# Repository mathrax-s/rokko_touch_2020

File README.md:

# rokko_touch_2020
EAGLE and KiCad files (PSoC4 flexible touch sensor)

</img>

</img>

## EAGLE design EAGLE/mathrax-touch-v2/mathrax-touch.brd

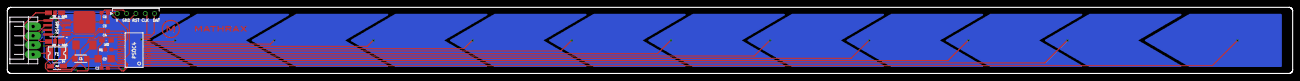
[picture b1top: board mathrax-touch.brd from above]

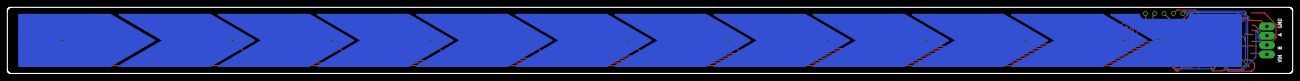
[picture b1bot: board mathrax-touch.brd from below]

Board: 2 copper layers, 350.0 x 18.0 mm, 31 parts (12 on the bottom side), 35 nets.

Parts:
C1: 0.33uF; 3216
C2, C5, C6: 0.1uF; 0603
C3: 22uF; 1210
C4: 2.2nF; 0603
F1: H1; RESETABLE-HUES
LED: LED; CHIPLED_0805
PSOC4: PSoC4; SSOP28
R1: 1k; 0603
RS485: RS485; SOIC127P600X175-8N
U$1: PINHEADER-5; PINHEADER-5L
U$2: TOUCH-PTN-3; TOUCH-PTN3
U$3, U$4, U$5, U$6, U$7, U$8, U$9, U$18, U$19, U$20: TOUCH-PTN-2; TOUCH-PTN2
U$11: EH4-UART
U$13: REGULATOR-TO252-3; BA33BC0FP
U$21: TOUCH-PTN-1; TOUCH-PTN1
U$22: DIODE-SS2040L
U$23, U$24: JUMPER
U$25: M-LOGO
U$27: MATHRAX-LOGO

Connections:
3.3V: C3.1, C5.1, C6.1, PSOC4.27, RS485.8, U$1.1, U$13.OUT
A: RS485.6, U$11.2, U$24.3
B: RS485.7, U$11.3, U$23.3
CLK: PSOC4.14, U$1.4
DAT: PSOC4.13, U$1.5
GND: C1.P$2, C2.2, C3.2, C4.2, C5.2, C6.2, LED.C, PSOC4.28, RS485.5, U$1.2, U$11.1, U$13.GND
LED: PSOC4.21, R1.1
unnamed: F1.1, U$22.P$1
unnamed: U$25.P$1, U$25.P$2
unnamed: U$27.1, U$27.2
unnamed: U$27.3, U$27.4
unnamed: U$27.5, U$27.6
unnamed: LED.A, R1.2
unnamed: C4.1, PSOC4.17
unnamed: C2.1, PSOC4.26
unnamed: C1.P$1, U$13.VIN, U$22.P$2
RS485-CE: PSOC4.18, RS485.2, RS485.3
RST: PSOC4.25, U$1.3
RX: PSOC4.15, U$24.2
RX-485: RS485.1, U$24.1
T1: PSOC4.1, U$21.P$1
T2: PSOC4.2, U$20.P$1
T3: PSOC4.3, U$19.P$1
T4: PSOC4.4, U$18.P$1
T5: PSOC4.5, U$9.P$1
T6: PSOC4.6, U$8.P$1
T7: PSOC4.7, U$7.P$1
T8: PSOC4.8, U$6.P$1
T9: PSOC4.9, U$5.P$1
T10: PSOC4.10, U$4.P$1
T11: PSOC4.11, U$3.P$1
T12: PSOC4.12, U$2.P$1
TX: PSOC4.16, U$23.2
TX-485: RS485.4, U$23.1
VIN: F1.2, U$11.4

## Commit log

2023-10-26 eagle files
2023-10-26 convert KiCad
2023-10-30 add PSoC4 source

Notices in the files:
parts and their libraries:
Capacitors-mathrax: Licensing: Creative Commons ShareAlike 4.0 International - https://creativecommons.org/licenses/by-sa/4.0
